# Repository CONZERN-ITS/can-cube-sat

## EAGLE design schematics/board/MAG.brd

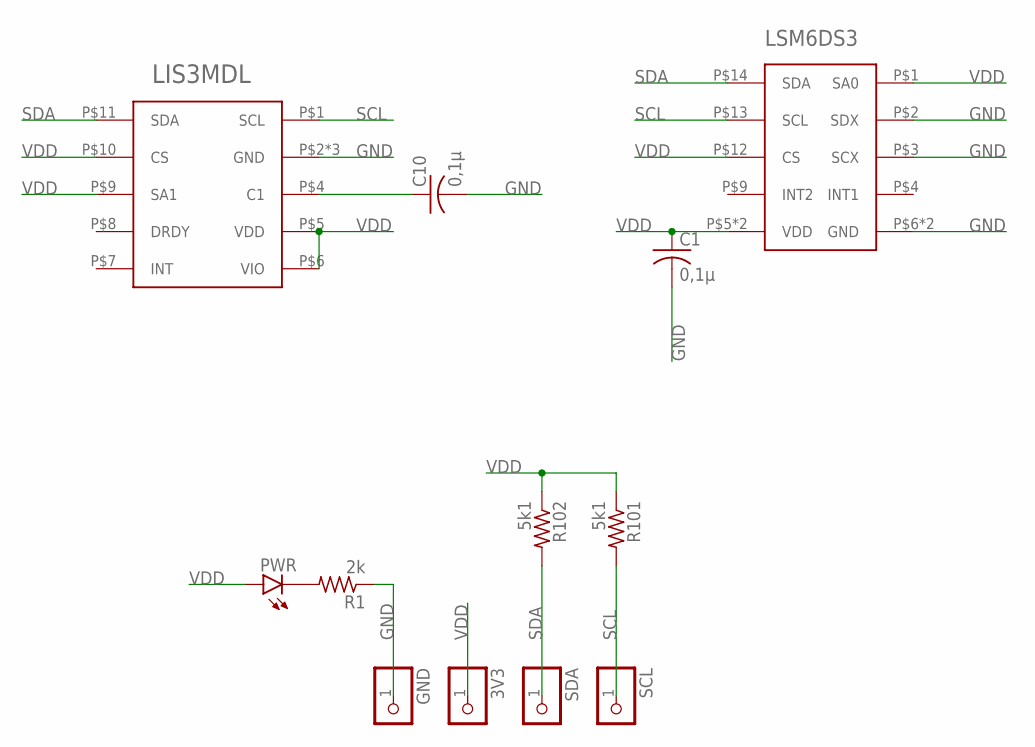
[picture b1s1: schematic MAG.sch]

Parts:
3V3: PINHD-1X1; 1X01
C1, C10: 0,1µ; C0603
GND: PINHD-1X1; 1X01
LIS3MDL: LIS3MDL
LSM6DS3: LSM6DS3
PWR: LEDCHIPLED_0603; CHIPLED_0603
R1: 2k; R0603
R101, R102: 5k1; R0603
SCL: PINHD-1X1; 1X01
SDA: PINHD-1X1; 1X01

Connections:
GND: C1.2, C10.2, GND.1, LIS3MDL.P$2 (GND), LIS3MDL.P$3 (GND), LIS3MDL.P$12 (GND), LSM6DS3.P$2 (SDX), LSM6DS3.P$3 (SCX), LSM6DS3.P$6 (GND), LSM6DS3.P$7 (GND), R1.1
unnamed: PWR.C, R1.2
unnamed: C10.1, LIS3MDL.P$4 (C1)
SCL: LIS3MDL.P$1 (SCL), LSM6DS3.P$13 (SCL), R101.2, SCL.1
SDA: LIS3MDL.P$11 (SDA), LSM6DS3.P$14 (SDA), R102.2, SDA.1
VDD: 3V3.1, C1.1, LIS3MDL.P$5 (VDD), LIS3MDL.P$6 (VIO), LIS3MDL.P$9 (SA1), LIS3MDL.P$10 (CS), LSM6DS3.P$1 (SA0), LSM6DS3.P$5 (VDD), LSM6DS3.P$8 (VDD), LSM6DS3.P$12 (CS), PWR.A, R101.1, R102.1

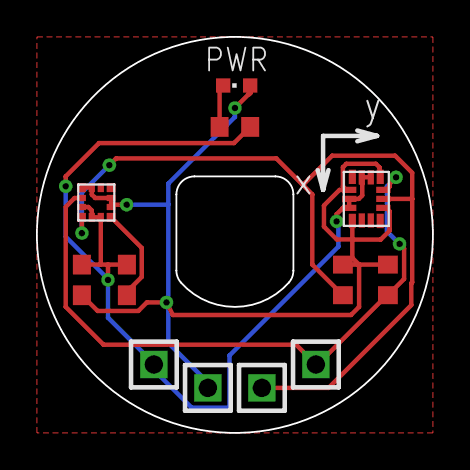
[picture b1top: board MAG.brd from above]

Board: 2 copper layers, 22.0 x 22.0 mm, 12 parts (0 on the bottom side), 6 nets.

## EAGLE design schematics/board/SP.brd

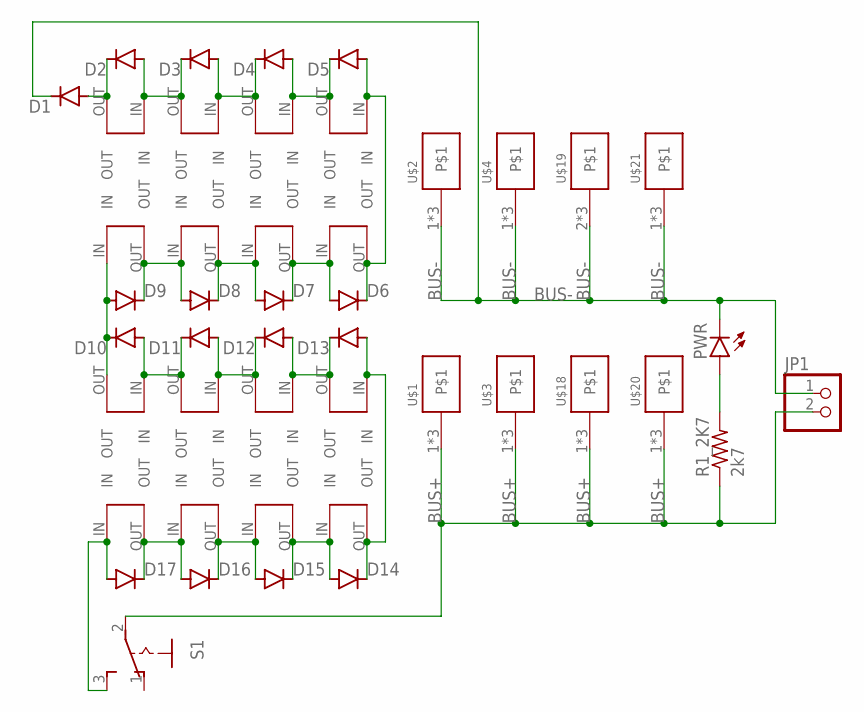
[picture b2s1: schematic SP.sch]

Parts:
D1, D2, D3, D4, D5, D6, D7, D8, D9, D10, D11, D12, D13, D14, D15, D16, D17: MBR0520LT; SOD123
JP1: PINHD-1X2; 1X02
PWR: LEDCHIPLED_0603; CHIPLED_0603
R1_2K7: 2k7; R0603
S1: 255SB
SOL1, SOL2, SOL3, SOL5, SOL6, SOL7, SOL9, SOL10, SOL11, SOL13, SOL14, SOL15: SOLAR_0
SOL4, SOL8, SOL12, SOL16: SOLAR_1
U$1, U$2, U$20, U$21: KCONNECT3; KCONNECT-3
U$3, U$4, U$18: KCONNECT4; KCONNECT-4
U$19: KCONNECT1; KCONNECT-1

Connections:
BUS+: JP1.2, R1_2K7.1, S1.2, U$1.1, U$1.2, U$1.4, U$3.1, U$3.2, U$3.3, U$18.1, U$18.2, U$18.3, U$20.1, U$20.2, U$20.4
BUS-: D1.C, JP1.1, PWR.C, U$2.1, U$2.2, U$2.4, U$4.1, U$4.2, U$4.3, U$19.2, U$19.3, U$19.4, U$21.1, U$21.2, U$21.4
unnamed: D16.A, D17.C, SOL1.OUT, SOL2.IN
unnamed: D15.A, D16.C, SOL2.OUT, SOL3.IN
unnamed: D1.A, D2.C, SOL16.OUT
unnamed: PWR.A, R1_2K7.2
unnamed: D14.A, D15.C, SOL3.OUT, SOL4.IN
unnamed: D17.A, S1.3 (S), SOL1.IN
unnamed: D12.A, D13.C, SOL5.OUT, SOL6.IN
unnamed: D11.A, D12.C, SOL6.OUT, SOL7.IN
unnamed: D10.A, D11.C, SOL7.OUT, SOL8.IN
unnamed: D9.A, D10.C, SOL8.OUT, SOL9.IN
unnamed: D8.A, D9.C, SOL9.OUT, SOL10.IN
unnamed: D7.A, D8.C, SOL10.OUT, SOL11.IN
unnamed: D6.A, D7.C, SOL11.OUT, SOL12.IN
unnamed: D5.A, D6.C, SOL12.OUT, SOL13.IN
unnamed: D4.A, D5.C, SOL13.OUT, SOL14.IN
unnamed: D3.A, D4.C, SOL14.OUT, SOL15.IN
unnamed: D2.A, D3.C, SOL15.OUT, SOL16.IN
unnamed: D13.A, D14.C, SOL4.OUT, SOL5.IN

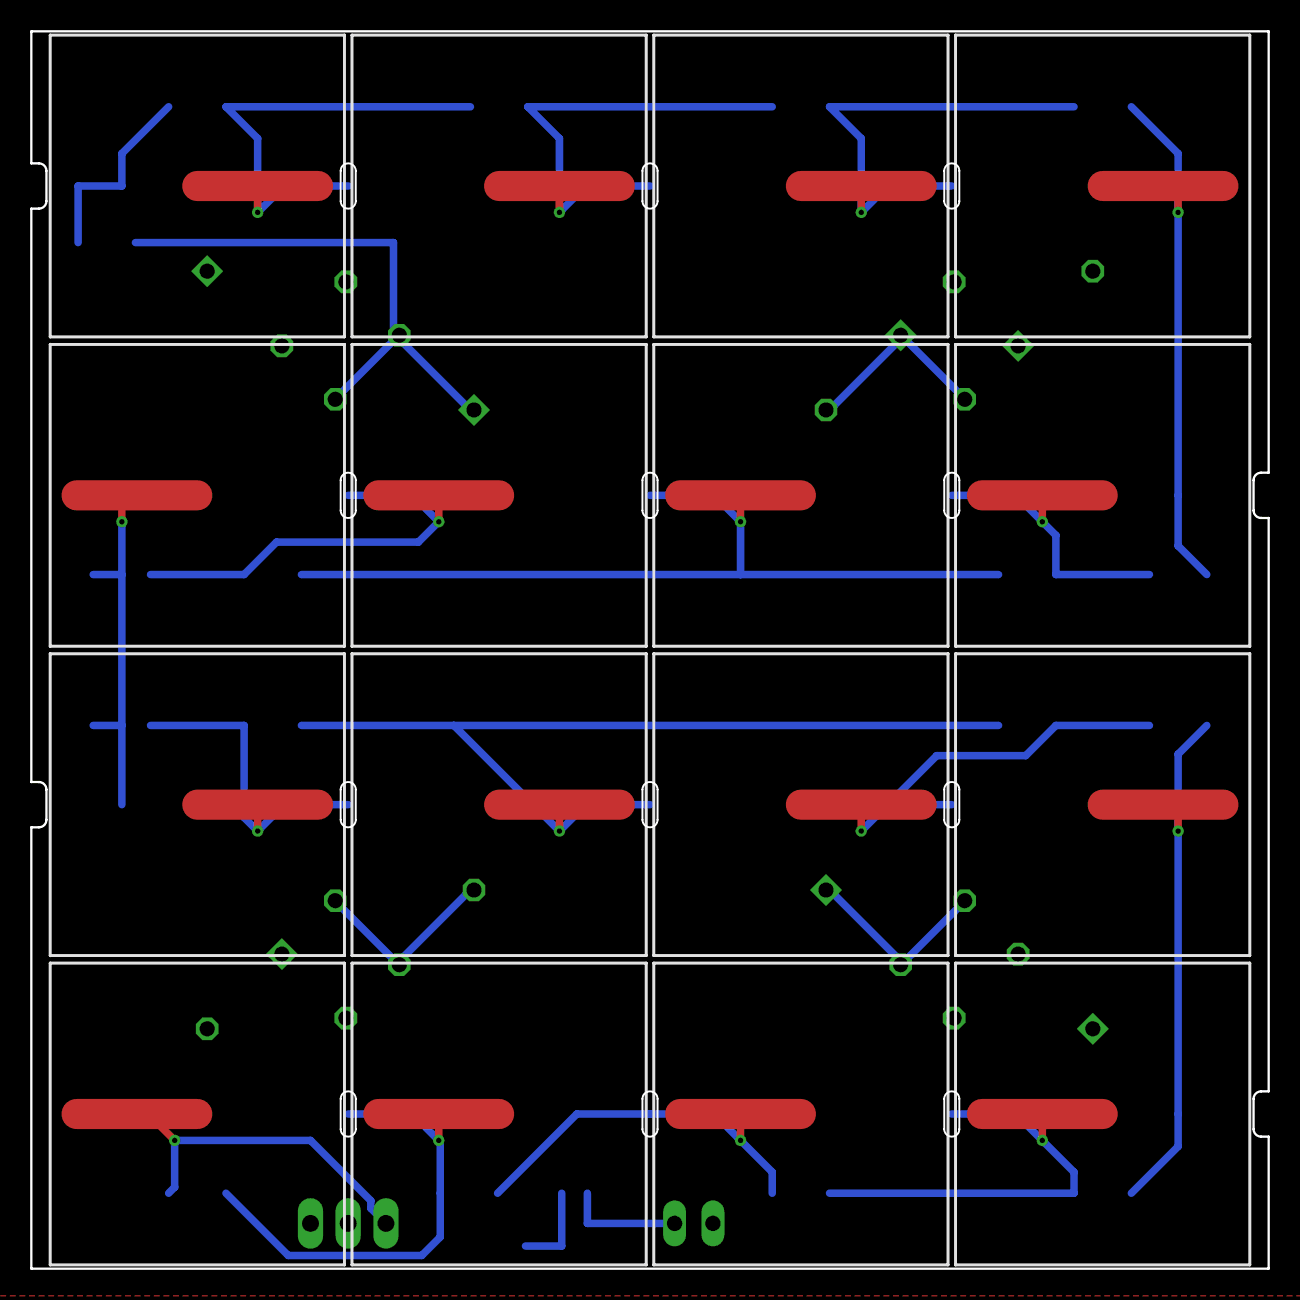
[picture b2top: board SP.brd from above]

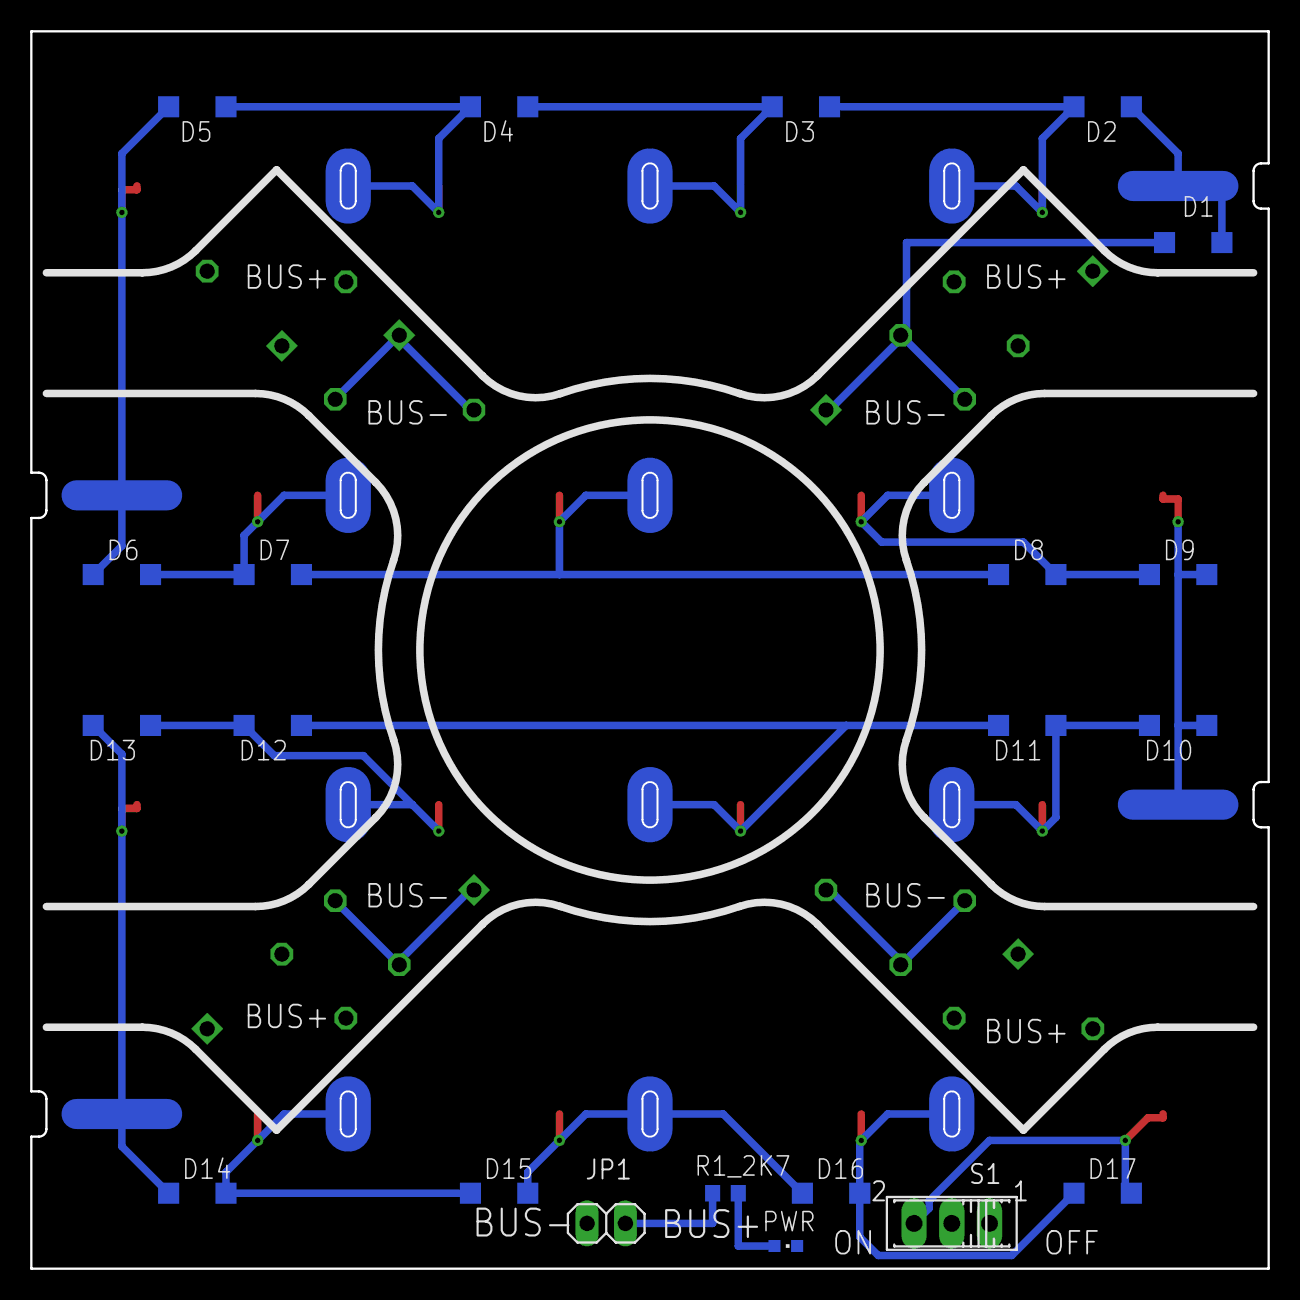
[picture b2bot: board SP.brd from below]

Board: 2 copper layers, 82.0 x 82.0 mm, 45 parts (29 on the bottom side), 20 nets.

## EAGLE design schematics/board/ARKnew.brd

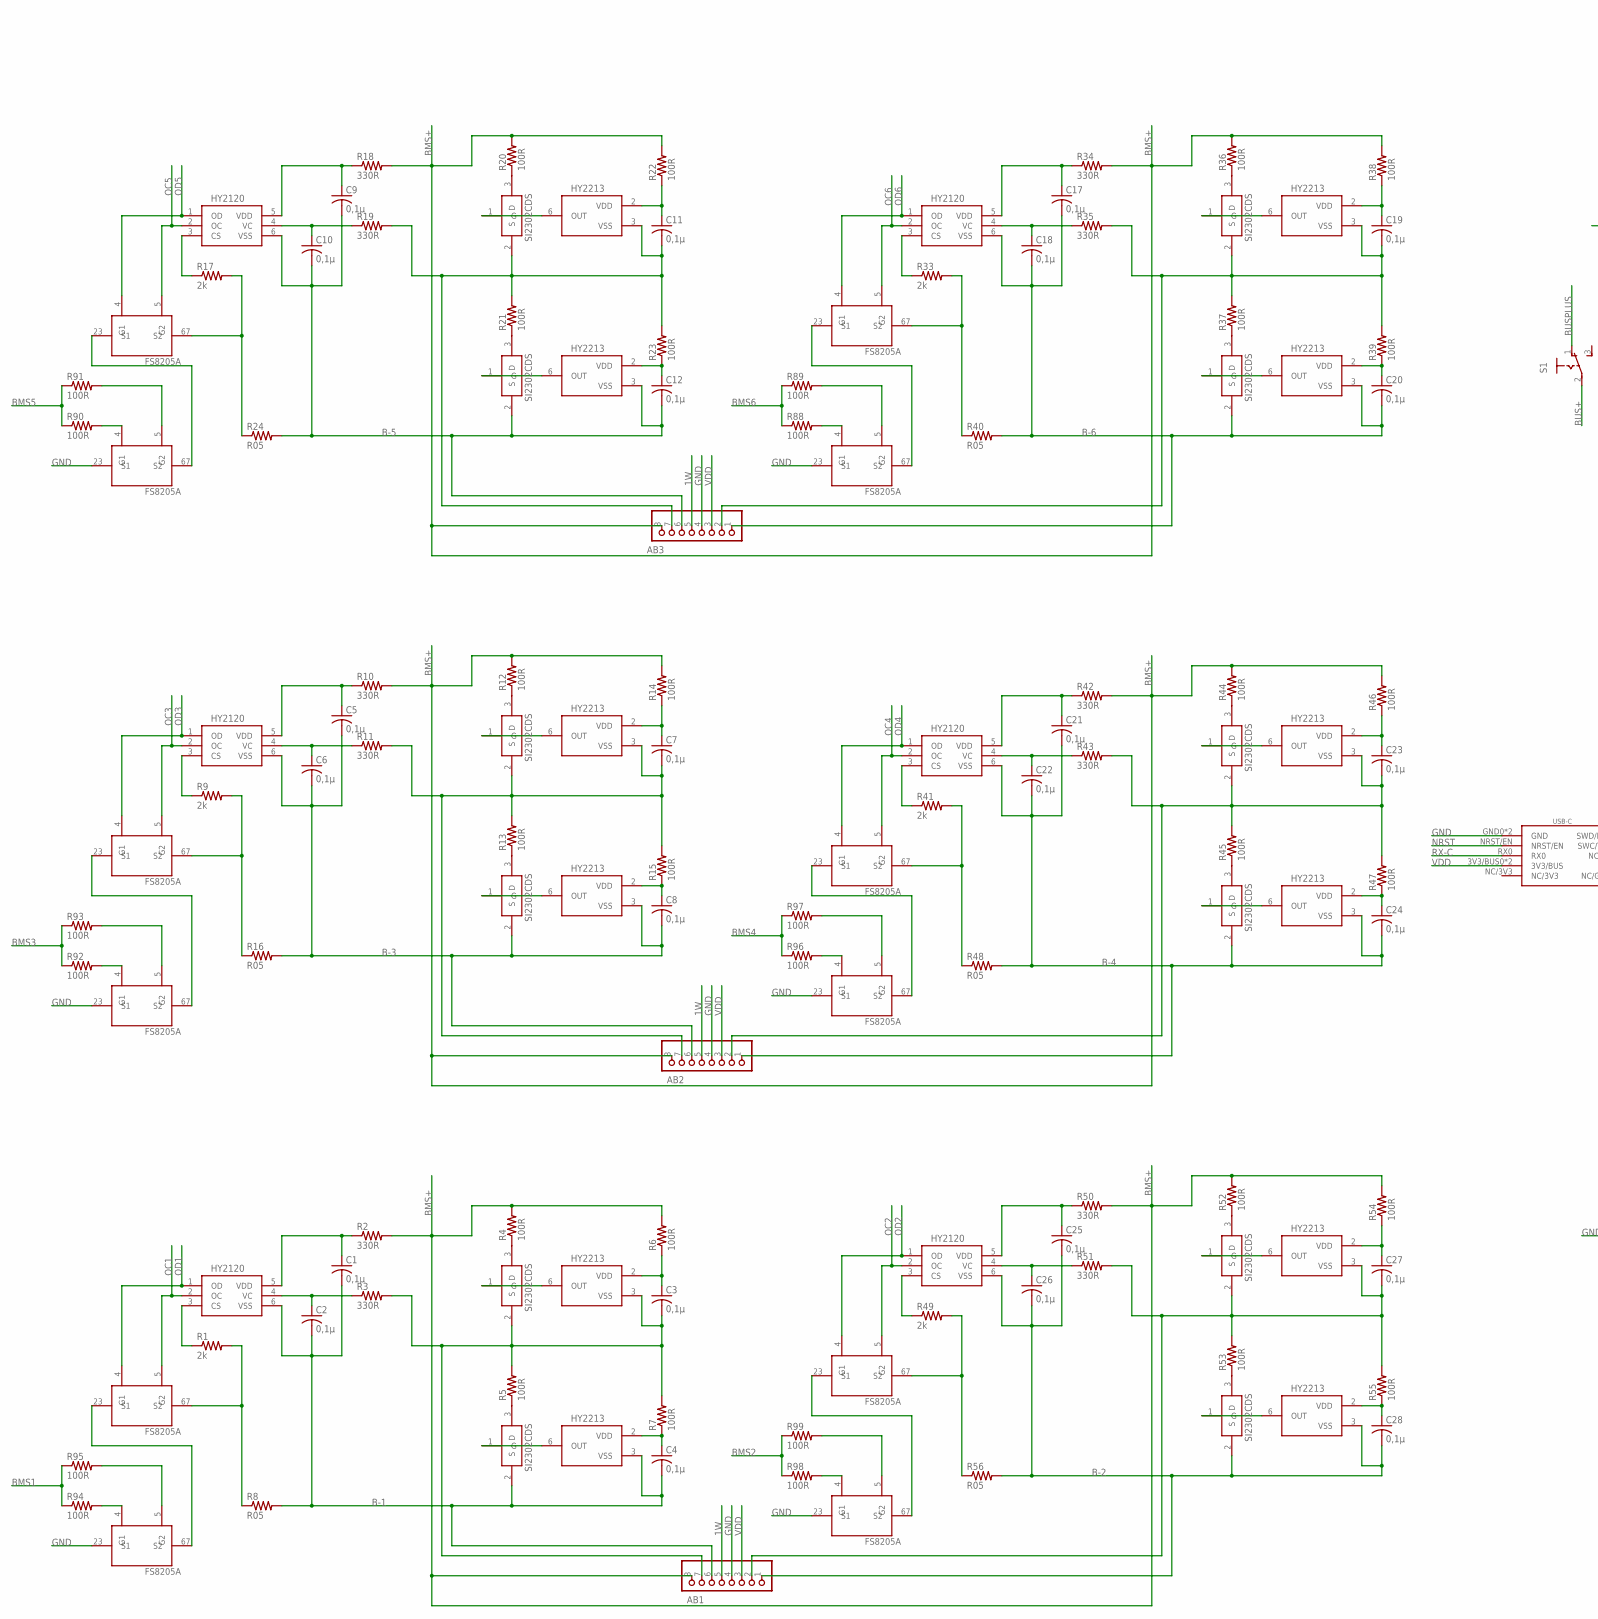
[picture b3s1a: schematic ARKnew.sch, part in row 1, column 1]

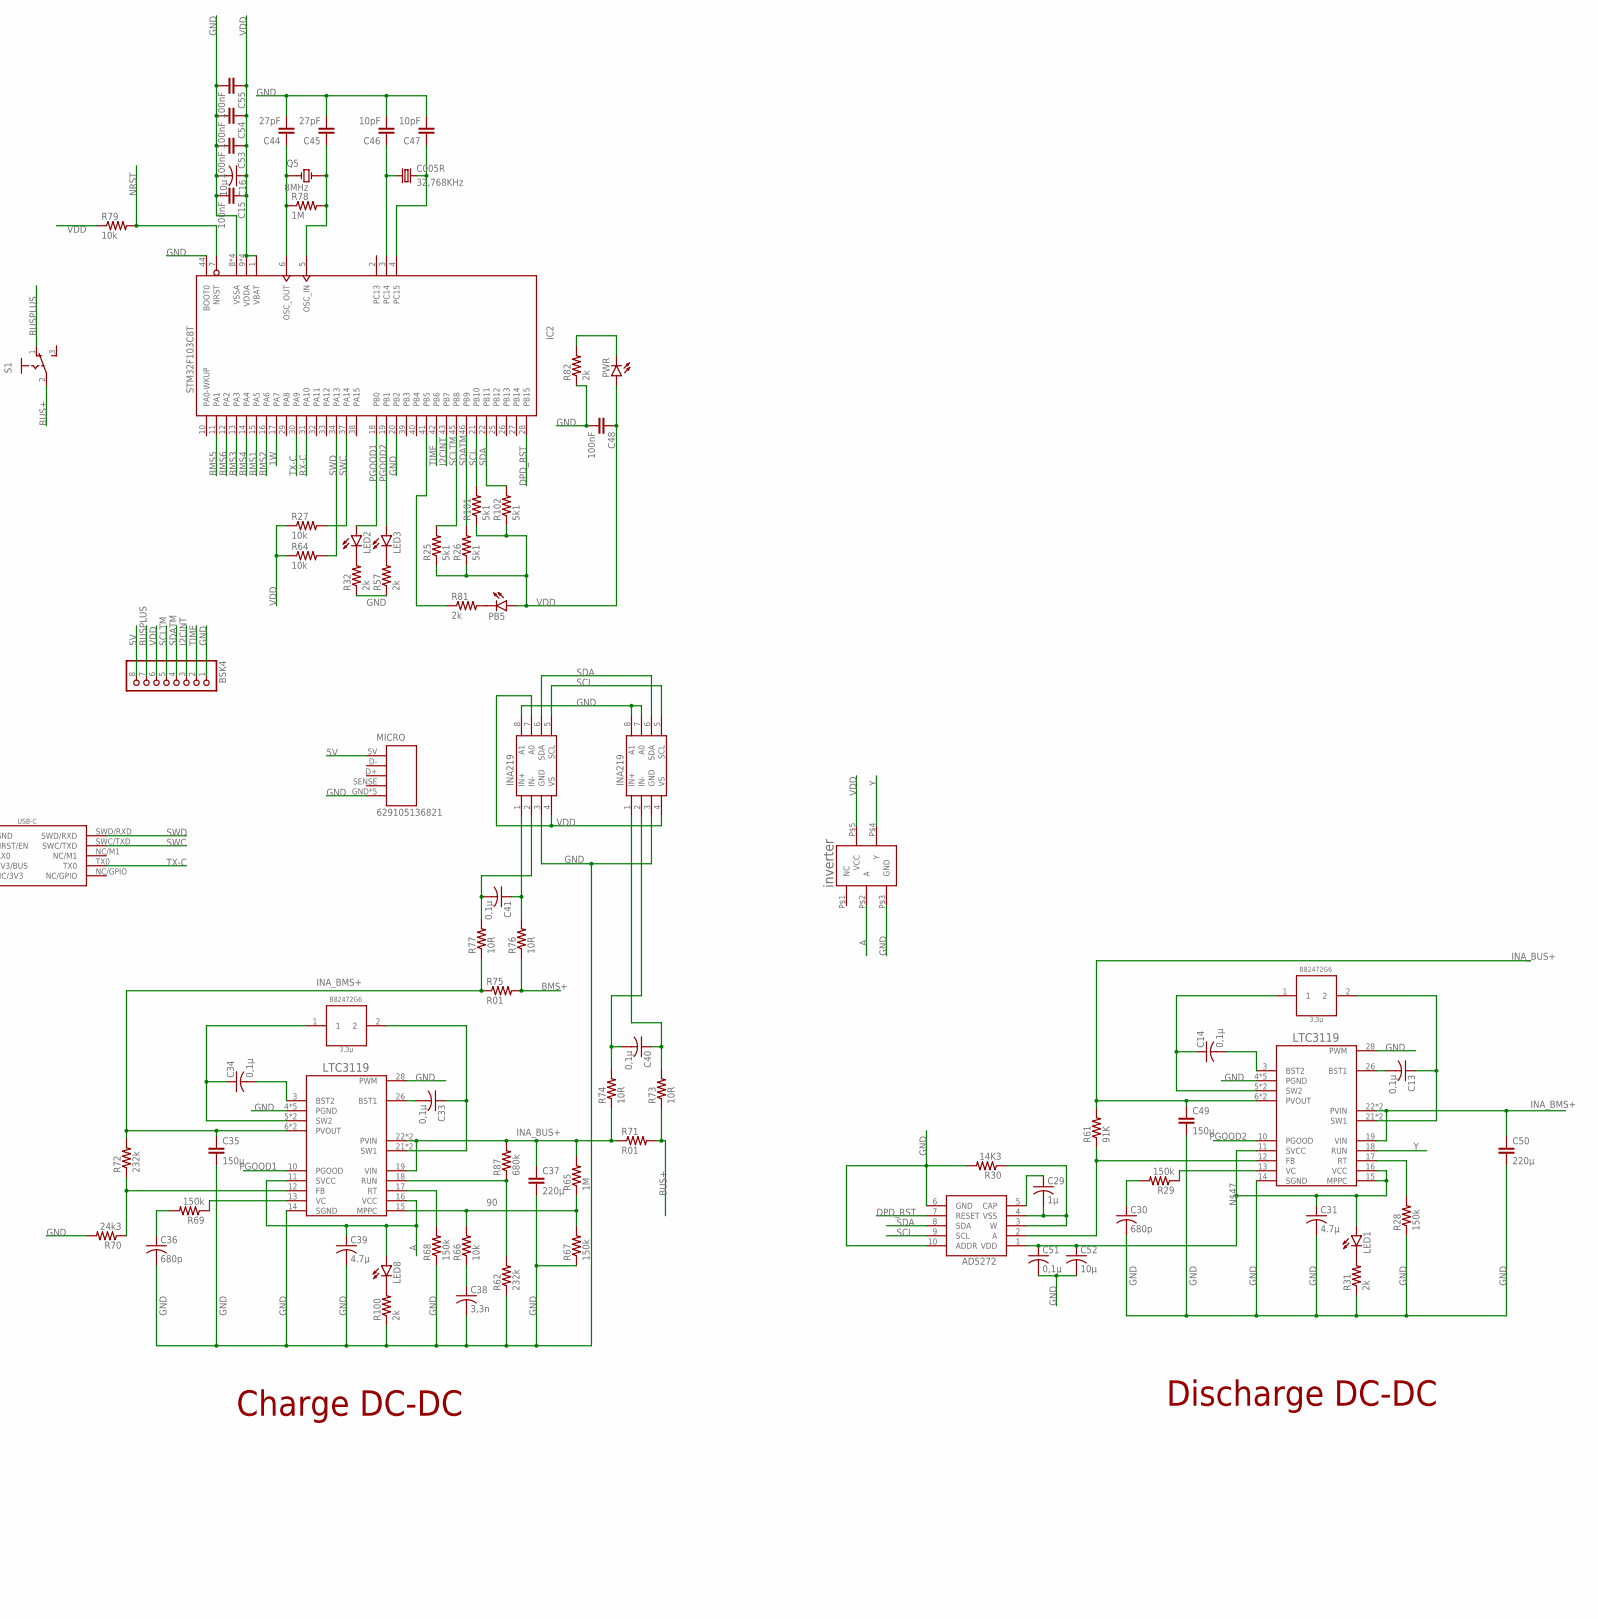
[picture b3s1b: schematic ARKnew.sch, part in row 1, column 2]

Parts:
3,3µH, 3,3µH1: 3,3µ; B82472G6
AB1, AB2, AB3: PINHD-1X8; 1X08
AD5272#2: AD5272
BSK4: PINHD-1X8; 1X08
C1, C2, C3, C4, C5, C6, C7, C8, C9, C10, C11, C12, C13, C14, C17, C18, C19, C20, C21, C22, C23, C24, C25, C26, C27, C28, C33, C34, C40, C41, C51: 0,1µ; C0603
C005R: 32,768KHz; C005R
C15, C48, C53, C54, C55: 100nF; C0603
C16, C52: 10µ; C1206
C29: 1µ; C0603
C30, C36: 680p; C0603
C31, C39: 4.7µ; C1206
C35, C49: 150µ; ECAP150
C37, C50: 220µ; ECAP220
C38: 3,3n; C0603
C44, C45: 27pF; C0603
C46, C47: 10pF; C0603
IC2: STM32F103C8T; LQFP48
INA219#1: INA219AID
LED1, LED2, LED3, LED8: LEDCHIPLED_0603; CHIPLED_0603
MICRO: 629105136821
PB5: LEDCHIPLED_0603; CHIPLED_0603
PWR: LEDCHIPLED_0603; CHIPLED_0603
Q5: 8MHz; XTAL_9C-8.000MEEJ-T
R1, R9, R17, R31, R32, R33, R41, R49, R57, R81, R82, R100: 2k; R0603
R2, R3, R10, R11, R18, R19, R34, R35, R42, R43, R50, R51: 330R; R0603
R4, R5, R6, R7, R12, R13, R14, R15, R20, R21, R22, R23, R36, R37, R38, R39, R44, R45, R46, R47, R52, R53, R54, R55, R88, R89, R90, R91, R92, R93, R94, R95, R96, R97, R98, R99: 100R; R0603
R8, R16, R24, R40, R48, R56: R05; R2512
R25, R26, R101, R102: 5k1; R0603
R27, R64, R66, R79: 10k; R0603
R28, R29, R67, R68, R69: 150k; R0603
R30: 14K3; R0603
R61: 91K; R0603
R62, R72: 232k; R0603
R65, R78: 1M; R0603
R70: 24k3; R0603
R71, R75: R01; R2512
R73, R74, R76, R77: 10R; R0603
R87: 680k; R0603
S1: UNICS-SWITCH
U$1, U$8, U$9, U$15, U$22, U$24, U$25, U$26, U$27, U$28, U$29, U$30: FS8205A-
U$2: INVERTER
U$3, U$10, U$17, U$31, U$38, U$45: HY2120
U$4, U$5, U$11, U$12, U$18, U$19, U$32, U$33, U$39, U$40, U$46, U$47: HY2213
U$6, U$7, U$13, U$14, U$20, U$21, U$34, U$35, U$41, U$42, U$48, U$49: SI2302CDS
U$16, U$59: LTC3119
U$23: USB-C
U$57: INA219AID

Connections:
1W: AB1.5, AB2.5, AB3.5, IC2.17 (PA7)
5V: BSK4.8, MICRO.5V (1)
90: R65.1, R66.2, R67.2, U$59.15 (MPPC)
A: C39.1, LED8.A, U$2.P$2 (A), U$59.11 (SVCC), U$59.16 (VCC)
B-1: AB1.6, C1.2, C2.2, C4.2, R8.2, U$3.6 (VSS), U$5.3 (VSS), U$7.2 (S)
B-2: AB1.1, C25.2, C26.2, C28.2, R56.2, U$45.6 (VSS), U$47.3 (VSS), U$49.2 (S)
B-3: AB2.6, C5.2, C6.2, C8.2, R16.2, U$10.6 (VSS), U$12.3 (VSS), U$14.2 (S)
B-4: AB2.1, C21.2, C22.2, C24.2, R48.2, U$38.6 (VSS), U$40.3 (VSS), U$42.2 (S)
B-5: AB3.6, C9.2, C10.2, C12.2, R24.2, U$17.6 (VSS), U$19.3 (VSS), U$21.2 (S)
B-6: AB3.1, C17.2, C18.2, C20.2, R40.2, U$31.6 (VSS), U$33.3 (VSS), U$35.2 (S)
BMS1: IC2.15 (PA5), R94.1, R95.1
BMS2: IC2.16 (PA6), R98.1, R99.1
BMS3: IC2.13 (PA3), R92.1, R93.1
BMS4: IC2.14 (PA4), R96.1, R97.1
BMS5: IC2.11 (PA1), R90.1, R91.1
BMS6: IC2.12 (PA2), R88.1, R89.1
BMS+: AB1.8, AB2.8, AB3.8, R2.2, R4.2, R6.2, R10.2, R12.2, R14.2, R18.2, R20.2, R22.2, R34.2, R36.2, R38.2, R42.2, R44.2, R46.2, R50.2, R52.2, R54.2, R75.2, R76.1
BUS+: R71.2, R73.1, S1.2
BUSPLUS: BSK4.7, S1.1 (O)
DPD_RST: AD5272#2.7 (RESET), IC2.28 (PB15)
GND: AB1.4, AB2.4, AB3.4, AD5272#2.6 (GND), AD5272#2.10 (ADDR), BSK4.1, C15.2, C16.2, C30.2, C31.2, C35.P$2 (2), C36.2, C37.P$2 (2), C38.2, C39.2, C44.2, C45.2, C46.2, C47.2, C48.2, C49.P$2 (2), C50.P$2 (2), C51.2, C52.2, C53.2, C54.2, C55.2, IC2.8 (VSSA), IC2.20 (PB2), IC2.23 (VSSA), IC2.35 (VSSA), IC2.44 (BOOT0), IC2.47 (VSSA), INA219#1.3 (GND), INA219#1.7 (A0), INA219#1.8 (A1), MICRO.GND (5), MICRO.Z1 (5), MICRO.Z2 (5), MICRO.Z3 (5), MICRO.Z4 (5), R28.1, R30.2, R31.1, R32.1, R57.1, R62.1, R67.1, R68.1, R70.2, R82.1, R100.1, U$2.P$3 (GND), U$9.23 (S1), U$16.4 (PGND), U$16.9 (PGND), U$16.14 (SGND), U$16.20 (PGND), U$16.25 (PGND), U$16.28 (PWM), U$16.29 (PGND), U$22.23 (S1), U$23.GND0 (GND), U$23.GND1 (GND), U$27.23 (S1), U$28.23 (S1), U$29.23 (S1), U$30.23 (S1), U$57.3 (GND), U$57.8 (A1), U$59.4 (PGND), U$59.9 (PGND), U$59.14 (SGND), U$59.20 (PGND), U$59.25 (PGND), U$59.28 (PWM), U$59.29 (PGND)
I2CINT: BSK4.3, IC2.43 (PB7)
INA_BMS+: C35.P$1 (1), C50.P$1 (1), R72.2, R75.1, R77.1, U$16.19 (VIN), U$16.22 (PVIN), U$16.23 (PVIN), U$59.6 (PVOUT), U$59.7 (PVOUT)
INA_BUS+: C37.P$1 (1), C49.P$1 (1), R61.2, R65.2, R71.1, R74.1, R87.2, U$16.6 (PVOUT), U$16.7 (PVOUT), U$59.19 (VIN), U$59.22 (PVIN), U$59.23 (PVIN)
unnamed: C1.1, R2.1, U$3.5 (VDD)
unnamed: C4.1, R7.1, U$5.2 (VDD)
unnamed: R1.1, U$3.3 (CS)
unnamed: C3.1, R6.1, U$4.2 (VDD)
unnamed: AD5272#2.2 (A), R61.1, U$16.12 (FB)
unnamed: U$4.6 (OUT), U$6.1 (G)
unnamed: R4.1, U$6.3 (D)
unnamed: AB1.7, C3.2, R3.2, R5.2, R7.2, U$4.3 (VSS), U$6.2 (S)
unnamed: U$5.6 (OUT), U$7.1 (G)
unnamed: R5.1, U$7.3 (D)
unnamed: 3,3µH1.2, C13.1, U$16.21 (SW1), U$16.24 (SW1)
unnamed: 3,3µH1.1, C14.1, U$16.5 (SW2), U$16.8 (SW2)
unnamed: R1.2, R8.1, U$26.67 (S2)
unnamed: C40.2, INA219#1.2 (IN-), R74.2
unnamed: C2.1, R3.1, U$3.4 (VC)
unnamed: C5.1, R10.1, U$10.5 (VDD)
unnamed: PB5.C, R81.2
unnamed: R9.1, U$10.3 (CS)
unnamed: C7.1, R14.1, U$11.2 (VDD)
unnamed: U$11.6 (OUT), U$13.1 (G)
unnamed: R12.1, U$13.3 (D)
unnamed: U$12.6 (OUT), U$14.1 (G)
unnamed: R13.1, U$14.3 (D)
unnamed: R9.2, R16.1, U$25.67 (S2)
unnamed: R70.1, R72.1, U$59.12 (FB)
unnamed: LED1.C, R31.2
unnamed: C6.1, R11.1, U$10.4 (VC)
unnamed: C8.1, R15.1, U$12.2 (VDD)
unnamed: R28.2, U$16.17 (RT)
unnamed: AB2.7, C7.2, R11.2, R13.2, R15.2, U$11.3 (VSS), U$13.2 (S)
unnamed: R91.2, U$9.5 (G2)
unnamed: C13.2, U$16.26 (BST1)
unnamed: C9.1, R18.1, U$17.5 (VDD)
unnamed: R17.1, U$17.3 (CS)
unnamed: C11.1, R22.1, U$18.2 (VDD)
unnamed: U$18.6 (OUT), U$20.1 (G)
unnamed: R20.1, U$20.3 (D)
unnamed: U$19.6 (OUT), U$21.1 (G)
unnamed: R21.1, U$21.3 (D)
unnamed: R17.2, R24.1, U$24.67 (S2)
unnamed: R29.1, U$16.13 (VC)
unnamed: C30.1, R29.2
unnamed: C10.1, R19.1, U$17.4 (VC)
unnamed: C12.1, R23.1, U$19.2 (VDD)
unnamed: R90.2, U$9.4 (G1)
unnamed: AB3.7, C11.2, R19.2, R21.2, R23.2, U$18.3 (VSS), U$20.2 (S)
unnamed: AD5272#2.1 (VDD), C31.1, C51.1, C52.1, LED1.A, U$16.11 (SVCC), U$16.15 (MPPC), U$16.16 (VCC)
unnamed: AD5272#2.3 (W), AD5272#2.4 (VSS), C29.2, R30.1
unnamed: U$15.23 (S1), U$22.67 (S2)
unnamed: U$9.67 (S2), U$24.23 (S1)
unnamed: AD5272#2.5 (CAP), C29.1
unnamed: C14.2, U$16.3 (BST2)
unnamed: R88.2, U$22.4 (G1)
unnamed: LED2.C, R32.2
unnamed: R62.2, R87.1, U$59.18 (RUN)
unnamed: LED3.C, R57.2
unnamed: R36.1, U$34.3 (D)
unnamed: R37.1, U$35.3 (D)
unnamed: R44.1, U$41.3 (D)
unnamed: LED8.C, R100.2
unnamed: R89.2, U$22.5 (G2)
unnamed: U$25.23 (S1), U$27.67 (S2)
unnamed: R93.2, U$27.5 (G2)
unnamed: R92.2, U$27.4 (G1)
unnamed: C17.1, R34.1, U$31.5 (VDD)
unnamed: R33.1, U$31.3 (CS)
unnamed: C19.1, R38.1, U$32.2 (VDD)
unnamed: U$32.6 (OUT), U$34.1 (G)
unnamed: R45.1, U$42.3 (D)
unnamed: U$33.6 (OUT), U$35.1 (G)
unnamed: R52.1, U$48.3 (D)
unnamed: R33.2, R40.1, U$15.67 (S2)
unnamed: U$8.23 (S1), U$28.67 (S2)
unnamed: R97.2, U$28.5 (G2)
unnamed: C18.1, R35.1, U$31.4 (VC)
unnamed: C20.1, R39.1, U$33.2 (VDD)
unnamed: R96.2, U$28.4 (G1)
unnamed: AB3.2, C19.2, R35.2, R37.2, R39.2, U$32.3 (VSS), U$34.2 (S)
unnamed: U$26.23 (S1), U$29.67 (S2)
unnamed: R95.2, U$29.5 (G2)
unnamed: C21.1, R42.1, U$38.5 (VDD)
unnamed: R41.1, U$38.3 (CS)
unnamed: C23.1, R46.1, U$39.2 (VDD)
unnamed: U$39.6 (OUT), U$41.1 (G)
unnamed: R53.1, U$49.3 (D)
unnamed: U$40.6 (OUT), U$42.1 (G)
unnamed: R41.2, R48.1, U$8.67 (S2)
unnamed: R94.2, U$29.4 (G1)
unnamed: U$1.23 (S1), U$30.67 (S2)
unnamed: C22.1, R43.1, U$38.4 (VC)
unnamed: C24.1, R47.1, U$40.2 (VDD)
unnamed: R99.2, U$30.5 (G2)
unnamed: AB2.2, C23.2, R43.2, R45.2, R47.2, U$39.3 (VSS), U$41.2 (S)
unnamed: R98.2, U$30.4 (G1)
unnamed: C25.1, R50.1, U$45.5 (VDD)
unnamed: R49.1, U$45.3 (CS)
unnamed: C27.1, R54.1, U$46.2 (VDD)
unnamed: U$46.6 (OUT), U$48.1 (G)
unnamed: U$47.6 (OUT), U$49.1 (G)
unnamed: R49.2, R56.1, U$1.67 (S2)
unnamed: C26.1, R51.1, U$45.4 (VC)
unnamed: C28.1, R55.1, U$47.2 (VDD)
unnamed: AB1.2, C27.2, R51.2, R53.2, R55.2, U$46.3 (VSS), U$48.2 (S)
unnamed: C34.2, U$59.3 (BST2)
unnamed: 3,3µH.2, C33.1, U$59.21 (SW1), U$59.24 (SW1)
unnamed: 3,3µH.1, C34.1, U$59.5 (SW2), U$59.8 (SW2)
unnamed: C44.1, IC2.6 (OSC_OUT), Q5.1, R78.1
unnamed: R69.1, U$59.13 (VC)
unnamed: C36.1, R69.2
unnamed: C38.1, R66.1
unnamed: R68.2, U$59.17 (RT)
unnamed: C33.2, U$59.26 (BST1)
unnamed: C45.1, IC2.5 (OSC_IN), Q5.2, R78.2
unnamed: C40.1, INA219#1.1 (IN+), R73.2
unnamed: C005R.P$2 (2), C47.1, IC2.4 (PC15)
unnamed: C41.1, R76.2, U$57.1 (IN+)
unnamed: C41.2, R77.2, U$57.2 (IN-)
unnamed: C005R.P$1 (1), C46.1, IC2.3 (PC14)
unnamed: PWR.C, R82.2
unnamed: IC2.41 (PB5), R81.1
NRST: IC2.7 (NRST), R79.2, U$23.NRST/EN
OC1: U$3.2 (OC), U$26.5 (G2)
OC2: U$1.5 (G2), U$45.2 (OC)
OC3: U$10.2 (OC), U$25.5 (G2)
OC4: U$8.5 (G2), U$38.2 (OC)
OC5: U$17.2 (OC), U$24.5 (G2)
OC6: U$15.5 (G2), U$31.2 (OC)
OD1: U$3.1 (OD), U$26.4 (G1)
OD2: U$1.4 (G1), U$45.1 (OD)
OD3: U$10.1 (OD), U$25.4 (G1)
OD4: U$8.4 (G1), U$38.1 (OD)
OD5: U$17.1 (OD), U$24.4 (G1)
OD6: U$15.4 (G1), U$31.1 (OD)
PGOOD1: IC2.18 (PB0), LED2.A, U$59.10 (PGOOD)
PGOOD2: IC2.19 (PB1), LED3.A, U$16.10 (PGOOD)
RX-C: IC2.31 (PA10), U$23.RX0
SCL: AD5272#2.9 (SCL), IC2.21 (PB10), INA219#1.5 (SCL), R101.2, U$57.5 (SCL)
SCLTM: BSK4.5, IC2.45 (PB8), R25.2
SDA: AD5272#2.8 (SDA), IC2.22 (PB11), INA219#1.6 (SDA), R102.2, U$57.6 (SDA)
SDATM: BSK4.4, IC2.46 (PB9), R26.2
SWC: IC2.37 (PA14), R27.2, U$23.SWC/TXD
SWD: IC2.34 (PA13), R64.2, U$23.SWD/RXD
TIME: BSK4.2, IC2.42 (PB6)
TX-C: IC2.30 (PA9), U$23.TX0
VDD: AB1.3, AB2.3, AB3.3, BSK4.6, C15.1, C16.1, C48.1, C53.1, C54.1, C55.1, IC2.1 (VBAT), IC2.9 (VDDA), IC2.24 (VDDA), IC2.36 (VDDA), IC2.48 (VDDA), INA219#1.4 (VS), PB5.A, PWR.A, R25.1, R26.1, R27.1, R64.1, R79.1, R101.1, R102.1, U$2.P$5 (VCC), U$23.3V3/BUS0 (3V3/BUS), U$23.3V3/BUS1 (3V3/BUS), U$57.4 (VS), U$57.7 (A0)
Y: U$2.P$4 (Y), U$16.18 (RUN)

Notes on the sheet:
Charge DC-DC
Discharge DC-DC

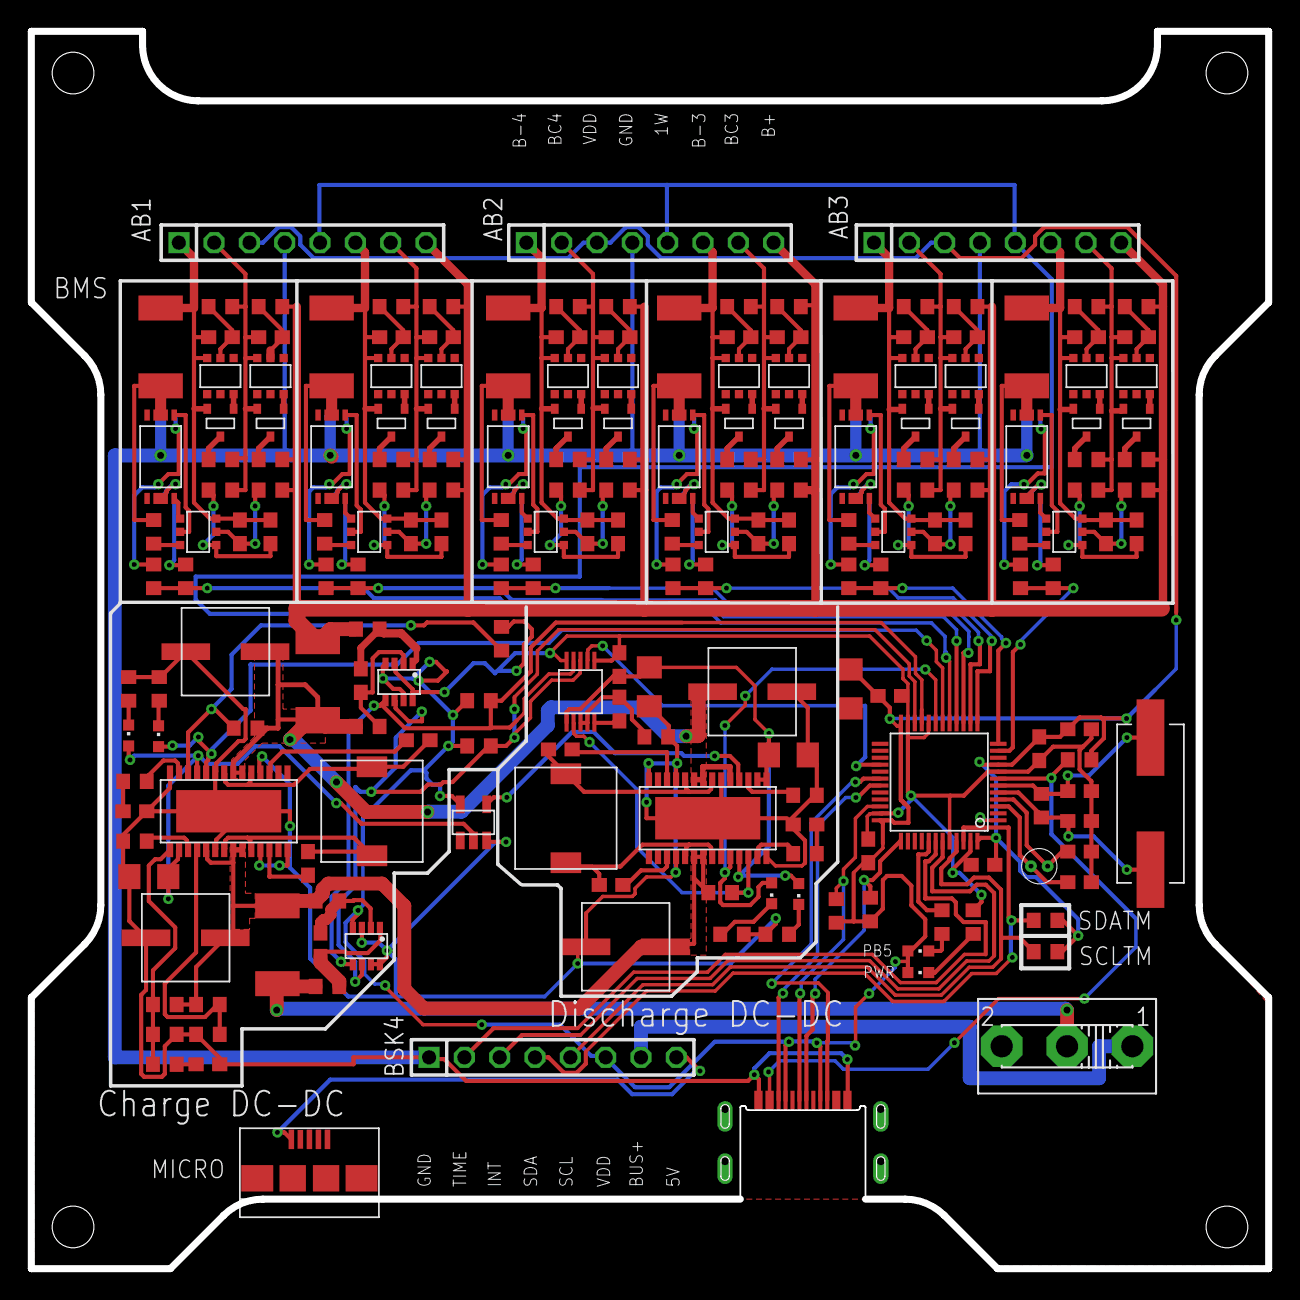
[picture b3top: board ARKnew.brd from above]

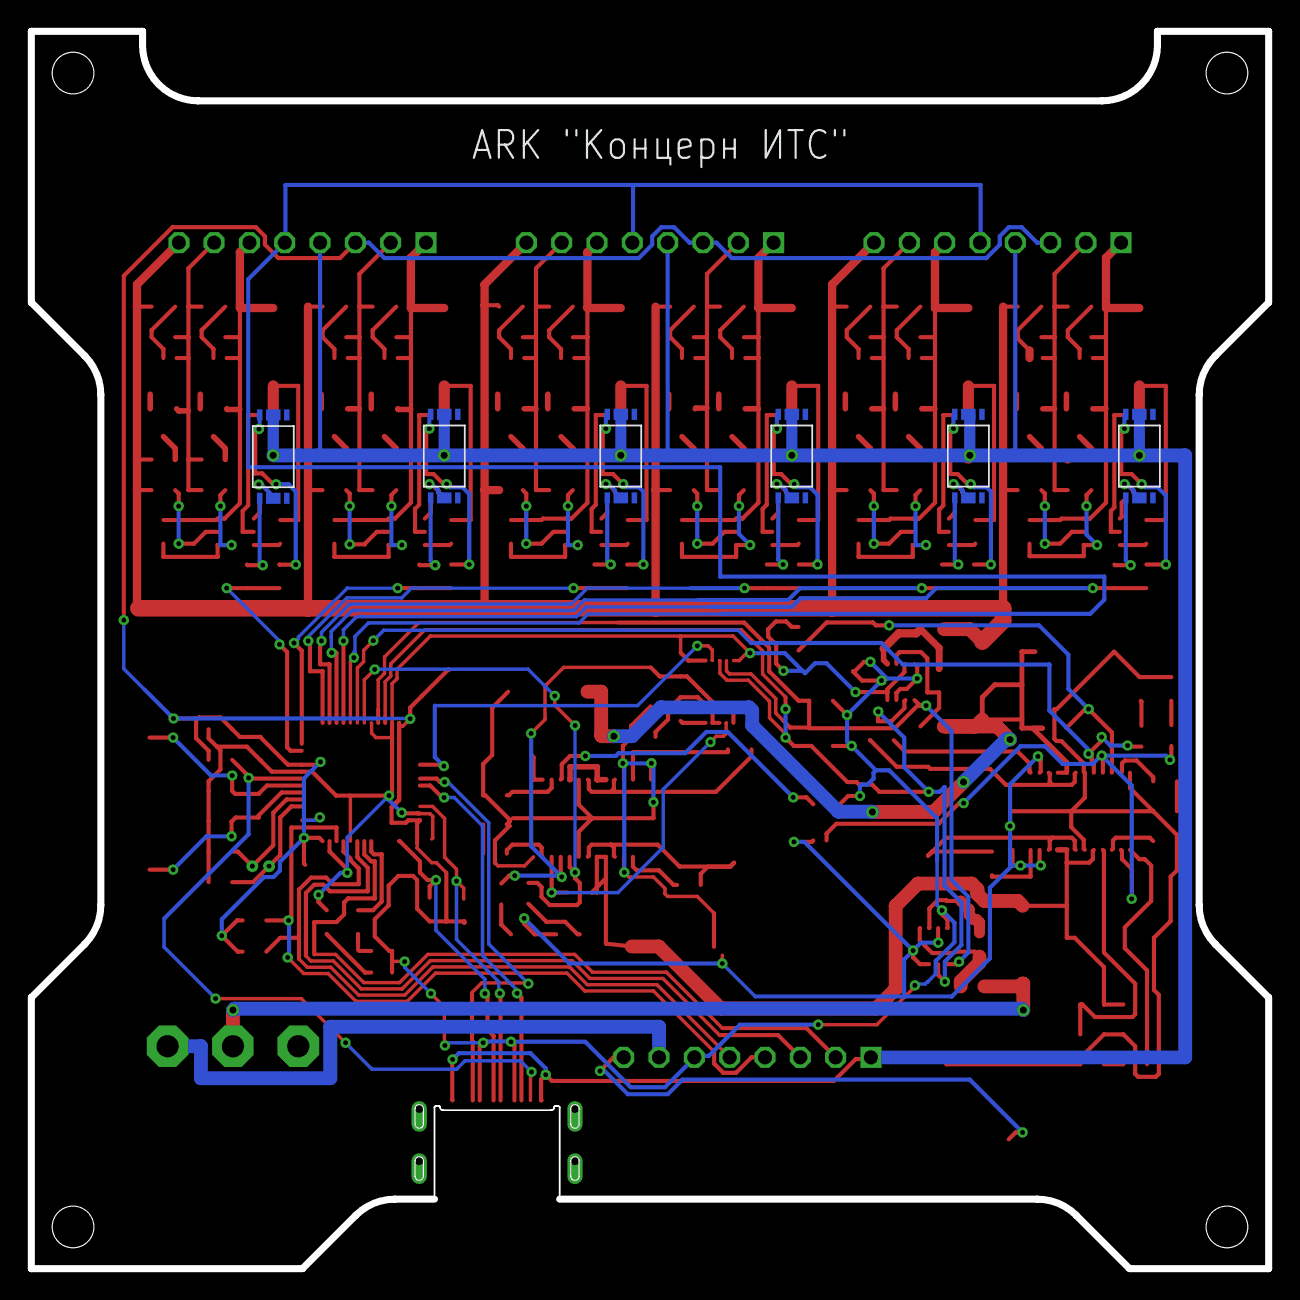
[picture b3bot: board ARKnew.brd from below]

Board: 2 copper layers, 89.0 x 89.0 mm, 211 parts (6 on the bottom side), 170 nets.

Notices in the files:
parts and their libraries:
MicroUSB: Copyright: Würth Elektronik
SparkFun-Batteries: Licensing: Creative Commons ShareAlike 4.0 International - https://creativecommons.org/licenses/by-sa/4.0
